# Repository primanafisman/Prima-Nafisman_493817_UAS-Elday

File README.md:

# Prima-Nafisman_493817_UAS-Elday
UAS Elektronika Daya

Nama  : Prima Nafisman

NIM   : 22/493817/TK/54121

Kelas : Elektronika Daya (A)

Go to Branches to access the my works

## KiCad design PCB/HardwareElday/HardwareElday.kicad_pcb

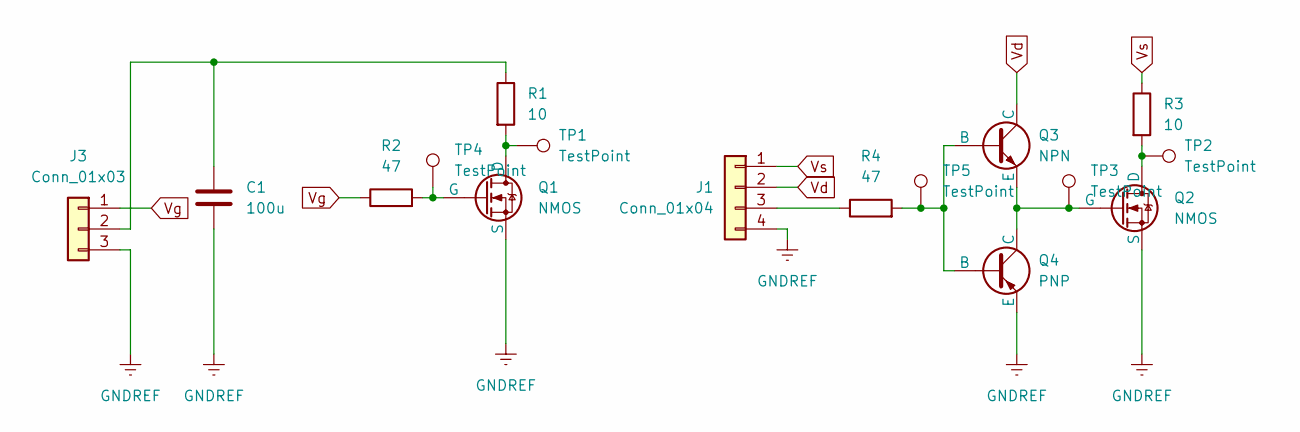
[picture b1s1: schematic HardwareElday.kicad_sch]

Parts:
C1: 100u; CP_Radial_D6.3mm_P2.50mm
J1: Conn_01x04; JST_XH_B4B-XH-A_1x04_P2.50mm_Vertical
J3: Conn_01x03; JST_XH_B3B-XH-A_1x03_P2.50mm_Vertical
Q1, Q2: NMOS; TO-220-3_Horizontal_TabDown
Q3: NPN; TO-92_Inline_Wide
Q4: PNP; TO-92_Inline_Wide
R1, R3: 10; R_Axial_DIN0411_L9.9mm_D3.6mm_P15.24mm_Horizontal
R2, R4: 47; R_Axial_DIN0207_L6.3mm_D2.5mm_P10.16mm_Horizontal
TP1, TP2, TP3, TP4, TP5: TestPoint; TestPoint_Loop_D2.60mm_Drill1.6mm_Beaded

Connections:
GNDREF: C1.2, J1.4, J3.3, Q1.3 (S), Q2.3 (S), Q4.1 (E)
unnamed: J1.3, R4.1
unnamed: C1.1, J3.2, R1.1
unnamed: Q1.2 (D), R1.2, TP1.1
unnamed: Q1.1 (G), R2.2, TP4.1
unnamed: Q2.2 (D), R3.2, TP2.1
unnamed: Q2.1 (G), Q3.1 (E), Q4.2 (C), TP3.1
unnamed: Q3.3 (B), Q4.3 (B), R4.2, TP5.1
Vd: J1.2, Q3.2 (C)
Vg: J3.1, R2.1
Vs: J1.1, R3.1

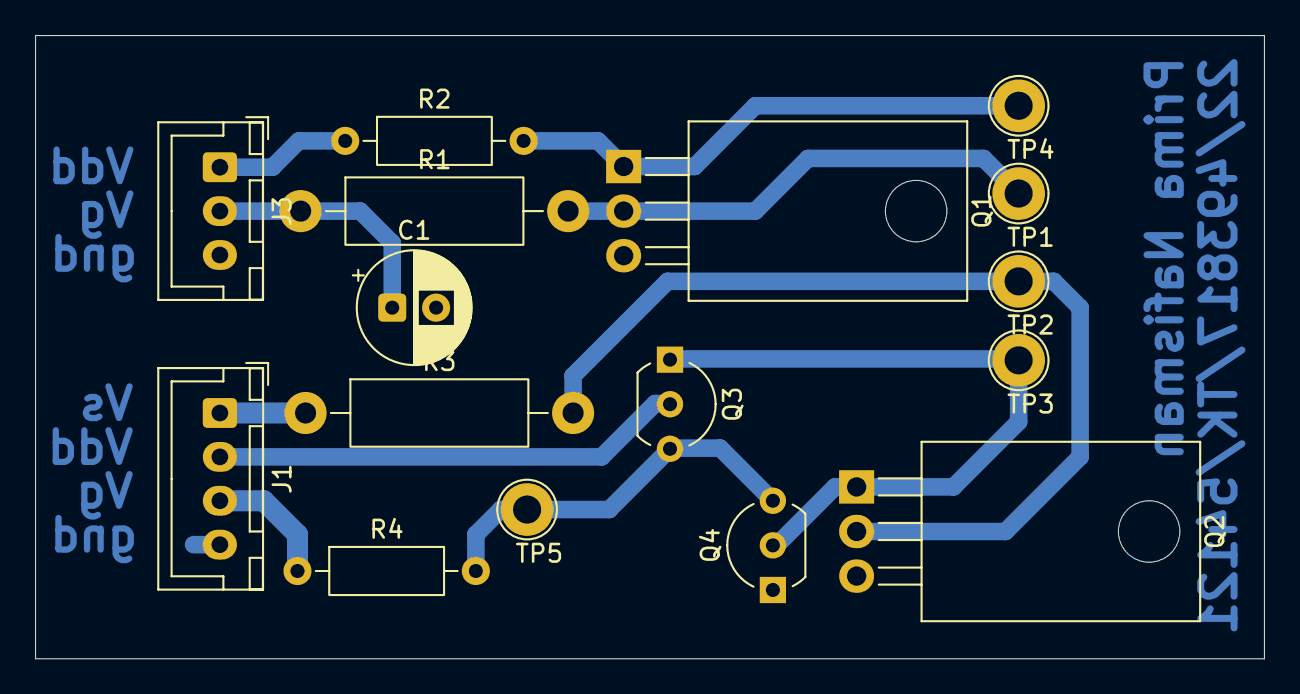
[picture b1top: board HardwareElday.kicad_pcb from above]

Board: 2 copper layers, 70.0 x 35.5 mm, 16 parts (0 on the bottom side), 11 nets.

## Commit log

2025-12-08 Project UAS Elektronika Daya
2025-12-08 Update file report and simulation
